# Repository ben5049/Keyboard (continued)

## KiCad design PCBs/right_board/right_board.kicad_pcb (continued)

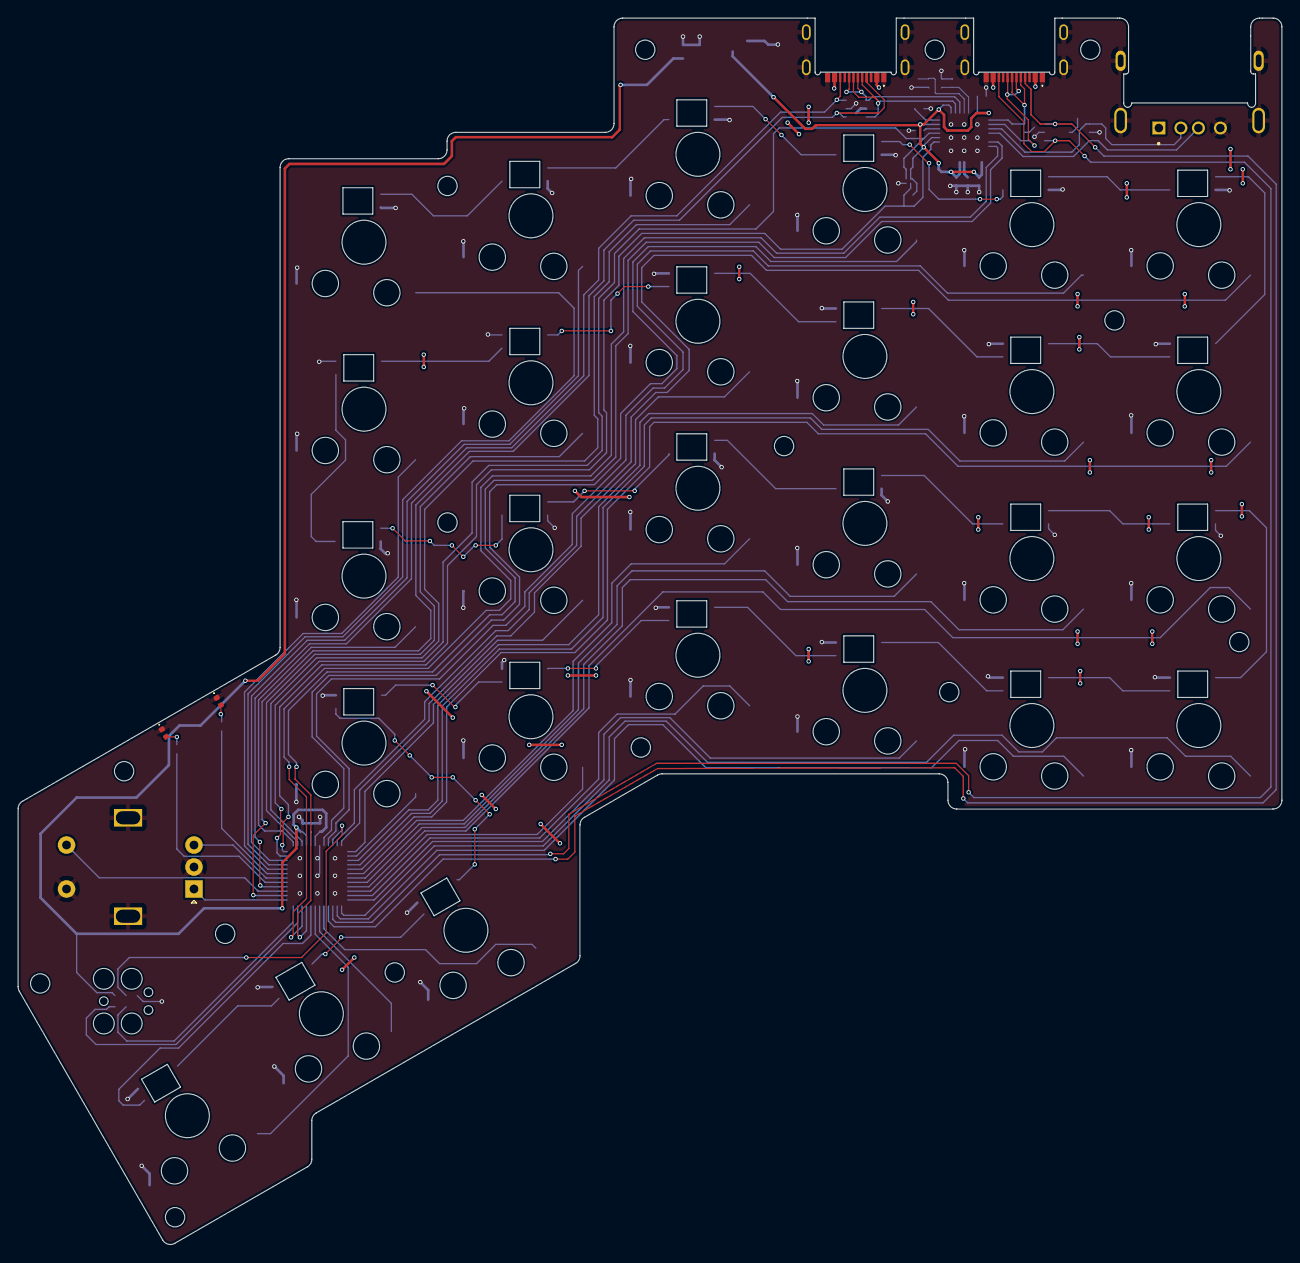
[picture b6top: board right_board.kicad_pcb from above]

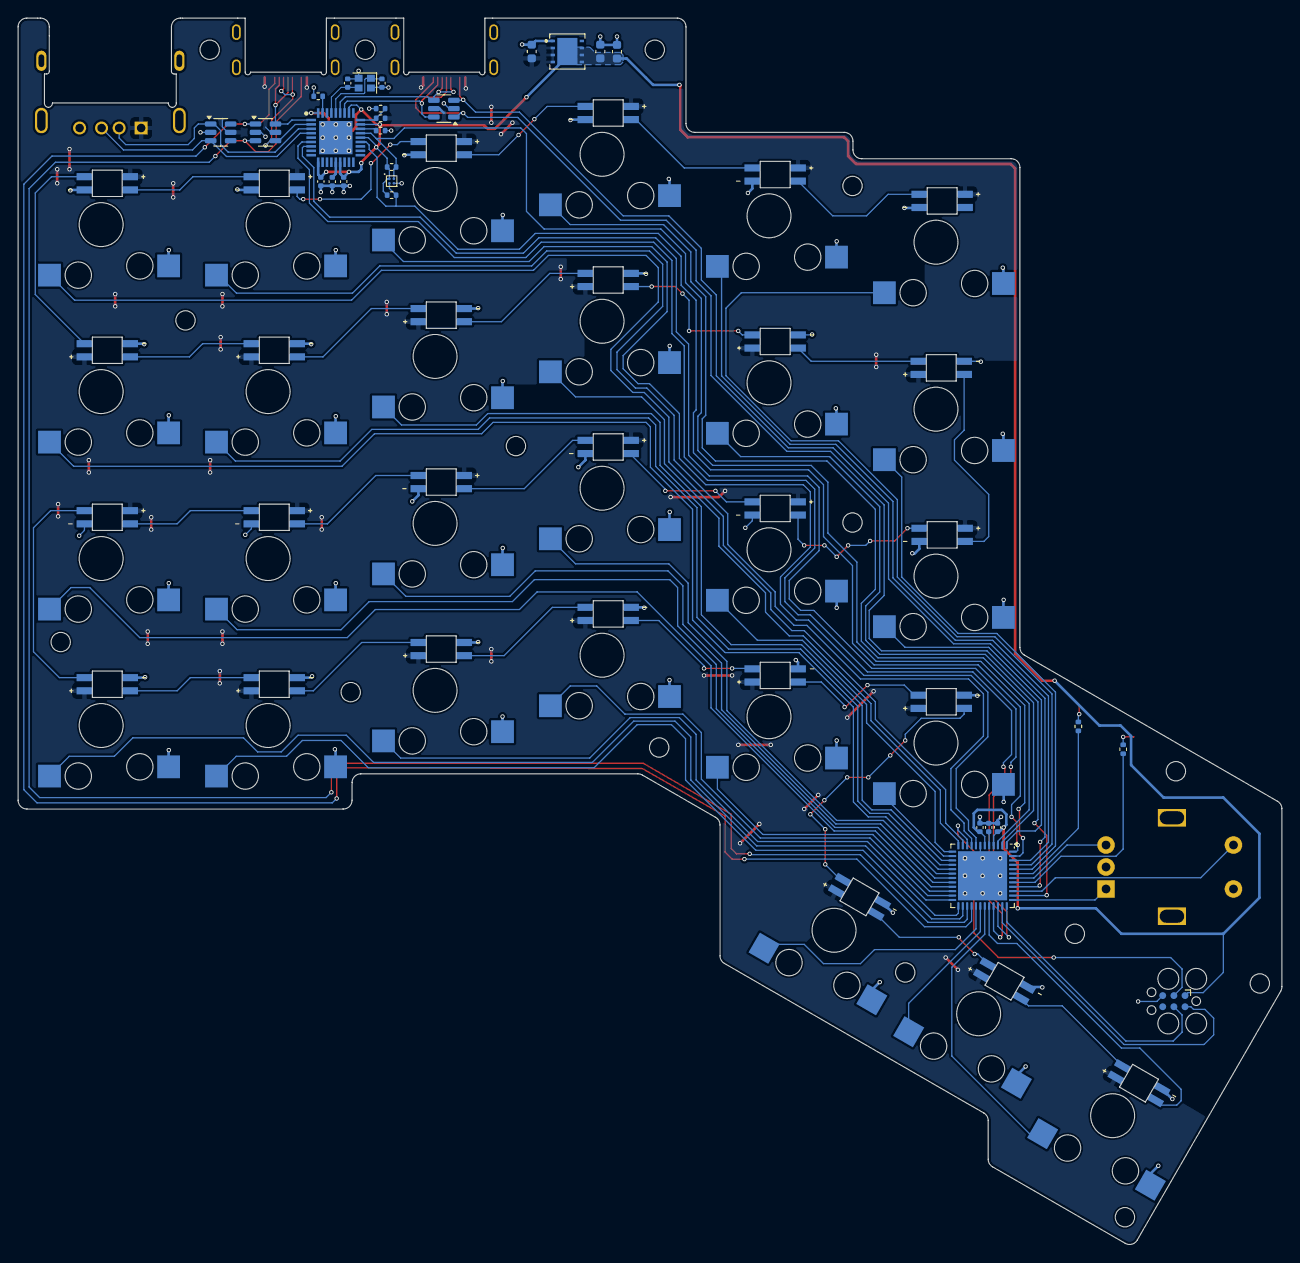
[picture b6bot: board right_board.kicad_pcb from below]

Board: 2 copper layers, 143.8 x 139.6 mm, 88 parts (55 on the bottom side), 88 nets.

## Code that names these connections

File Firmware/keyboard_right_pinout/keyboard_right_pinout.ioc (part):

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Mcu.Name=STM32G0C1C(C-E)Ux
Mcu.Package=UFQFPN48
Mcu.UserName=STM32G0C1CEUx
PA0.GPIOParameters=GPIO_PuPd,GPIO_Label
PA0.GPIO_Label=KEY_A12
PA0.GPIO_PuPd=GPIO_PULLUP
PA0.Signal=GPIO_Input
PA1.GPIOParameters=GPIO_PuPd,GPIO_Label
PA1.GPIO_Label=KEY_B9
PA1.GPIO_PuPd=GPIO_PULLUP
PA1.Signal=GPIO_Input
PA10.GPIOParameters=GPIO_Label
PA10.GPIO_Label=NEOPIXEL
PA10.Signal=S_TIM1_CH3
PA11\ [PA9].Mode=Device
PA11\ [PA9].Signal=USB_DM
PA12\ [PA10].Mode=Device
PA12\ [PA10].Signal=USB_DP
PA13.Mode=Serial_Wire
PA13.Signal=SYS_SWDIO
PA14-BOOT0.Mode=Serial_Wire
PA14-BOOT0.Signal=SYS_SWCLK
PA15.Signal=S_TIM2_CH1_ETR
PA2.GPIOParameters=GPIO_PuPd,GPIO_Label
PA2.GPIO_Label=KEY_C8
PA2.GPIO_PuPd=GPIO_PULLUP
PA2.Signal=GPIO_Input
PA3.GPIOParameters=GPIO_PuPd,GPIO_Label
PA3.GPIO_Label=KEY_D7
PA3.GPIO_PuPd=GPIO_PULLUP
PA3.Signal=GPIO_Input
PA4.GPIOParameters=GPIO_PuPd,GPIO_Label
PA4.GPIO_Label=KEY_B10
PA4.GPIO_PuPd=GPIO_PULLUP
PA4.Signal=GPIO_Input
PA5.GPIOParameters=GPIO_PuPd,GPIO_Label
PA5.GPIO_Label=KEY_B11
PA5.GPIO_PuPd=GPIO_PULLUP
PA5.Signal=GPIO_Input
PA6.GPIOParameters=GPIO_PuPd,GPIO_Label
PA6.GPIO_Label=KEY_B12
PA6.GPIO_PuPd=GPIO_PULLUP
PA6.Signal=GPIO_Input
PA7.GPIOParameters=GPIO_PuPd,GPIO_Label
PA7.GPIO_Label=KEY_C9
PA7.GPIO_PuPd=GPIO_PULLUP
PA7.Signal=GPIO_Input
PA8.Mode=Dual_Role_AllSignals
PA8.Signal=UCPD1_CC1
PA9.GPIOParameters=GPIO_PuPd,GPIO_Label
PA9.GPIO_Label=KEY_E6
PA9.GPIO_PuPd=GPIO_PULLUP
PA9.Signal=GPIO_Input
PB0.GPIOParameters=GPIO_PuPd,GPIO_Label
PB0.GPIO_Label=KEY_C10
PB0.GPIO_PuPd=GPIO_PULLUP
PB0.Signal=GPIO_Input
PB1.GPIOParameters=GPIO_PuPd,GPIO_Label
PB1.GPIO_Label=KEY_C11
PB1.GPIO_PuPd=GPIO_PULLUP
PB1.Signal=GPIO_Input
PB10.GPIOParameters=GPIO_PuPd,GPIO_Label
PB10.GPIO_Label=KEY_D8
PB10.GPIO_PuPd=GPIO_PULLUP
PB10.Signal=GPIO_Input
PB11.GPIOParameters=GPIO_PuPd,GPIO_Label
PB11.GPIO_Label=KEY_D9
PB11.GPIO_PuPd=GPIO_PULLUP
PB11.Signal=GPIO_Input
PB12.GPIOParameters=GPIO_PuPd,GPIO_Label
PB12.GPIO_Label=KEY_D10
PB12.GPIO_PuPd=GPIO_PULLUP
PB12.Signal=GPIO_Input
PB13.GPIOParameters=GPIO_PuPd,GPIO_Label
PB13.GPIO_Label=KEY_D12
PB13.GPIO_PuPd=GPIO_PULLUP
PB13.Signal=GPIO_Input
PB14.GPIOParameters=GPIO_PuPd,GPIO_Label
PB14.GPIO_Label=KEY_D11
PB14.GPIO_PuPd=GPIO_PULLUP
PB14.Signal=GPIO_Input
PB15.Mode=Dual_Role_AllSignals
PB15.Signal=UCPD1_CC2
PB2.GPIOParameters=GPIO_PuPd,GPIO_Label
PB2.GPIO_Label=KEY_C12
PB2.GPIO_PuPd=GPIO_PULLUP
PB2.Signal=GPIO_Input
PB3.Signal=S_TIM2_CH2
PB4.GPIOParameters=GPIO_Label
PB4.GPIO_Label=STAT1_LED
PB4.Signal=GPIO_Output
PB5.GPIOParameters=GPIO_PuPd,GPIO_Label
PB5.GPIO_Label=KEY_B7
PB5.GPIO_PuPd=GPIO_PULLUP
PB5.Signal=GPIO_Input
PB6.GPIOParameters=GPIO_PuPd,GPIO_Label
PB6.GPIO_Label=KEY_A7
PB6.GPIO_PuPd=GPIO_PULLUP
PB6.Signal=GPIO_Input
PB7.GPIOParameters=GPIO_PuPd,GPIO_Label
PB7.GPIO_Label=KEY_A8
PB7.GPIO_PuPd=GPIO_PULLUP
PB7.Signal=GPIO_Input
PB8.Mode=I2C
PB8.Signal=I2C1_SCL
PB9.Mode=I2C
PB9.Signal=I2C1_SDA
PC13.GPIOParameters=GPIO_PuPd,GPIO_Label
PC13.GPIO_Label=KEY_C7
PC13.GPIO_PuPd=GPIO_PULLUP
PC13.Signal=GPIO_Input
PC14-OSC32_IN\ (PC14).GPIOParameters=GPIO_PuPd,GPIO_Label
PC14-OSC32_IN\ (PC14).GPIO_Label=KEY_B8
PC14-OSC32_IN\ (PC14).GPIO_PuPd=GPIO_PULLUP
PC14-OSC32_IN\ (PC14).Signal=GPIO_Input
PC15-OSC32_OUT\ (PC15).GPIOParameters=GPIO_PuPd,GPIO_Label
PC15-OSC32_OUT\ (PC15).GPIO_Label=KEY_A9
PC15-OSC32_OUT\ (PC15).GPIO_PuPd=GPIO_PULLUP
PC15-OSC32_OUT\ (PC15).Signal=GPIO_Input
PC6.GPIOParameters=GPIO_PuPd,GPIO_Label
PC6.GPIO_Label=KEY_E5
PC6.GPIO_PuPd=GPIO_PULLUP
PC6.Signal=GPIO_Input
PC7.GPIOParameters=GPIO_PuPd,GPIO_Label
PC7.GPIO_Label=KEY_E4
PC7.GPIO_PuPd=GPIO_PULLUP
PC7.Signal=GPIO_Input
PD0.Mode=Dual_Role_AllSignals
PD0.Signal=UCPD2_CC1
PD1.GPIOParameters=GPIO_PuPd,GPIO_Label
PD1.GPIO_Label=ENC_SW
PD1.GPIO_PuPd=GPIO_PULLUP
PD1.Signal=GPIO_Input
PD2.Mode=Dual_Role_AllSignals
PD2.Signal=UCPD2_CC2
PD3.GPIOParameters=GPIO_Label
PD3.GPIO_Label=STAT2_LED
PD3.Signal=GPIO_Output
PF0-OSC_IN\ (PF0).GPIOParameters=GPIO_PuPd,GPIO_Label
PF0-OSC_IN\ (PF0).GPIO_Label=KEY_A10
PF0-OSC_IN\ (PF0).GPIO_PuPd=GPIO_PULLUP
PF0-OSC_IN\ (PF0).Signal=GPIO_Input
PF1-OSC_OUT\ (PF1).GPIOParameters=GPIO_PuPd,GPIO_Label
PF1-OSC_OUT\ (PF1).GPIO_Label=KEY_A11
PF1-OSC_OUT\ (PF1).GPIO_PuPd=GPIO_PULLUP
PF1-OSC_OUT\ (PF1).Signal=GPIO_Input
RCC.HSE_VALUE=8000000
RCC.SYSCLKFreq_VALUE=64000000
RCC.SYSCLKSource=RCC_SYSCLKSOURCE_PLLCLK
board=custom

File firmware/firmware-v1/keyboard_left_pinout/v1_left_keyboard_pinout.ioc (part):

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Mcu.Name=STM32G0C1C(C-E)Ux
Mcu.Package=UFQFPN48
Mcu.UserName=STM32G0C1CEUx
PA0.GPIOParameters=GPIO_PuPd,GPIO_Label
PA0.GPIO_Label=KEY_C1
PA0.GPIO_PuPd=GPIO_PULLUP
PA0.Signal=GPIO_Input
PA1.GPIOParameters=GPIO_PuPd,GPIO_Label
PA1.GPIO_Label=KEY_C2
PA1.GPIO_PuPd=GPIO_PULLUP
PA1.Signal=GPIO_Input
PA10.GPIOParameters=GPIO_PuPd,GPIO_Label
PA10.GPIO_Label=KEY_A6
PA10.GPIO_PuPd=GPIO_PULLUP
PA10.Signal=GPIO_Input
PA11\ [PA9].Mode=Device
PA11\ [PA9].Signal=USB_DM
PA12\ [PA10].Mode=Device
PA12\ [PA10].Signal=USB_DP
PA13.Mode=Serial_Wire
PA13.Signal=SYS_SWDIO
PA14-BOOT0.Mode=Serial_Wire
PA14-BOOT0.Signal=SYS_SWCLK
PA15.GPIOParameters=GPIO_PuPd,GPIO_Label
PA15.GPIO_Label=KEY_B6
PA15.GPIO_PuPd=GPIO_PULLUP
PA15.Signal=GPIO_Input
PA2.GPIOParameters=GPIO_PuPd,GPIO_Label
PA2.GPIO_Label=KEY_C3
PA2.GPIO_PuPd=GPIO_PULLUP
PA2.Signal=GPIO_Input
PA3.GPIOParameters=GPIO_PuPd,GPIO_Label
PA3.GPIO_Label=KEY_C4
PA3.GPIO_PuPd=GPIO_PULLUP
PA3.Signal=GPIO_Input
PA4.GPIOParameters=GPIO_PuPd,GPIO_Label
PA4.GPIO_Label=KEY_D5
PA4.GPIO_PuPd=GPIO_PULLUP
PA4.Signal=GPIO_Input
PA5.GPIOParameters=GPIO_PuPd,GPIO_Label
PA5.GPIO_Label=KEY_B1
PA5.GPIO_PuPd=GPIO_PULLUP
PA5.Signal=GPIO_Input
PA6.GPIOParameters=GPIO_PuPd,GPIO_Label
PA6.GPIO_Label=KEY_B2
PA6.GPIO_PuPd=GPIO_PULLUP
PA6.Signal=GPIO_Input
PA7.GPIOParameters=GPIO_PuPd,GPIO_Label
PA7.GPIO_Label=KEY_B3
PA7.GPIO_PuPd=GPIO_PULLUP
PA7.Signal=GPIO_Input
PA8.Mode=Dual_Role_AllSignals
PA8.Signal=UCPD1_CC1
PA9.GPIOParameters=GPIO_PuPd,GPIO_Label
PA9.GPIO_Label=KEY_D6
PA9.GPIO_PuPd=GPIO_PULLUP
PA9.Signal=GPIO_Input
PB0.GPIOParameters=GPIO_PuPd,GPIO_Label
PB0.GPIO_Label=KEY_B4
PB0.GPIO_PuPd=GPIO_PULLUP
PB0.Signal=GPIO_Input
PB1.GPIOParameters=GPIO_PuPd,GPIO_Label
PB1.GPIO_Label=KEY_A1
PB1.GPIO_PuPd=GPIO_PULLUP
PB1.Signal=GPIO_Input
PB10.GPIOParameters=GPIO_PuPd,GPIO_Label
PB10.GPIO_Label=KEY_A2
PB10.GPIO_PuPd=GPIO_PULLUP
PB10.Signal=GPIO_Input
PB11.GPIOParameters=GPIO_PuPd,GPIO_Label
PB11.GPIO_Label=KEY_B5
PB11.GPIO_PuPd=GPIO_PULLUP
PB11.Signal=GPIO_Input
PB12.GPIOParameters=GPIO_PuPd,GPIO_Label
PB12.GPIO_Label=KEY_A3
PB12.GPIO_PuPd=GPIO_PULLUP
PB12.Signal=GPIO_Input
PB13.Mode=I2C
PB13.Signal=I2C2_SCL
PB14.Mode=I2C
PB14.Signal=I2C2_SDA
PB15.Mode=Dual_Role_AllSignals
PB15.Signal=UCPD1_CC2
PB2.GPIOParameters=GPIO_PuPd,GPIO_Label
PB2.GPIO_Label=KEY_C5
PB2.GPIO_PuPd=GPIO_PULLUP
PB2.Signal=GPIO_Input
PB3.GPIOParameters=GPIO_Label
PB3.GPIO_Label=STAT2_LED
PB3.Signal=GPIO_Output
PB4.GPIOParameters=GPIO_Label
PB4.GPIO_Label=ENC_A
PB4.Signal=S_TIM3_CH1
PB5.GPIOParameters=GPIO_Label
PB5.GPIO_Label=ENC_B
PB5.Signal=S_TIM3_CH2
PB6.GPIOParameters=GPIO_PuPd,GPIO_Label
PB6.GPIO_Label=ENC_SW
PB6.GPIO_PuPd=GPIO_PULLUP
PB6.Signal=GPIO_Input
PB7.GPIOParameters=GPIO_Label
PB7.GPIO_Label=NEOPIXEL
PB7.Signal=S_TIM4_CH2
PB8.GPIOParameters=GPIO_PuPd,GPIO_Label
PB8.GPIO_Label=KEY_E3
PB8.GPIO_PuPd=GPIO_PULLUP
PB8.Signal=GPIO_Input
PB9.GPIOParameters=GPIO_PuPd,GPIO_Label
PB9.GPIO_Label=KEY_E2
PB9.GPIO_PuPd=GPIO_PULLUP
PB9.Signal=GPIO_Input
PC13.GPIOParameters=GPIO_PuPd,GPIO_Label
PC13.GPIO_Label=KEY_E1
PC13.GPIO_PuPd=GPIO_PULLUP
PC13.Signal=GPIO_Input
PC14-OSC32_IN\ (PC14).GPIOParameters=GPIO_PuPd,GPIO_Label
PC14-OSC32_IN\ (PC14).GPIO_Label=KEY_D1
PC14-OSC32_IN\ (PC14).GPIO_PuPd=GPIO_PULLUP
PC14-OSC32_IN\ (PC14).Signal=GPIO_Input
PC15-OSC32_OUT\ (PC15).GPIOParameters=GPIO_PuPd,GPIO_Label
PC15-OSC32_OUT\ (PC15).GPIO_Label=KEY_D2
PC15-OSC32_OUT\ (PC15).GPIO_PuPd=GPIO_PULLUP
PC15-OSC32_OUT\ (PC15).Signal=GPIO_Input
PC6.GPIOParameters=GPIO_PuPd,GPIO_Label
PC6.GPIO_Label=KRY_A4
PC6.GPIO_PuPd=GPIO_PULLUP
PC6.Signal=GPIO_Input
PC7.GPIOParameters=GPIO_PuPd,GPIO_Label
PC7.GPIO_Label=KEY_A5
PC7.GPIO_PuPd=GPIO_PULLUP
PC7.Signal=GPIO_Input
PD0.Mode=Dual_Role_AllSignals
PD0.Signal=UCPD2_CC1
PD1.GPIOParameters=GPIO_PuPd,GPIO_Label
PD1.GPIO_Label=KEY_C6
PD1.GPIO_PuPd=GPIO_PULLUP
PD1.Signal=GPIO_Input
PD2.Mode=Dual_Role_AllSignals
PD2.Signal=UCPD2_CC2
PD3.GPIOParameters=GPIO_Label
PD3.GPIO_Label=STAT1_LED
PD3.Signal=GPIO_Output
PF0-OSC_IN\ (PF0).GPIOParameters=GPIO_PuPd,GPIO_Label
PF0-OSC_IN\ (PF0).GPIO_Label=KEY_D3
PF0-OSC_IN\ (PF0).GPIO_PuPd=GPIO_PULLUP
PF0-OSC_IN\ (PF0).Signal=GPIO_Input
PF1-OSC_OUT\ (PF1).GPIOParameters=GPIO_PuPd,GPIO_Label
PF1-OSC_OUT\ (PF1).GPIO_Label=KEY_D4
PF1-OSC_OUT\ (PF1).GPIO_PuPd=GPIO_PULLUP
PF1-OSC_OUT\ (PF1).Signal=GPIO_Input
RCC.HSE_VALUE=8000000
RCC.SYSCLKFreq_VALUE=64000000
RCC.SYSCLKSource=RCC_SYSCLKSOURCE_PLLCLK
board=custom

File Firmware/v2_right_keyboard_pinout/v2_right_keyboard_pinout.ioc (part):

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Mcu.Name=STM32U5G9ZJJxQ
Mcu.Package=UFBGA144
Mcu.UserName=STM32U5G9ZJJxQ
PA11.Mode=Internal_Phy_Device
PA11.Signal=USB_OTG_HS_DM
PA12.Mode=Internal_Phy_Device
PA12.Signal=USB_OTG_HS_DP
PA13\ (JTMS/SWDIO).Mode=Serial_Wire
PA13\ (JTMS/SWDIO).Signal=DEBUG_JTMS-SWDIO
PA14\ (JTCK/SWCLK).Mode=Serial_Wire
PA14\ (JTCK/SWCLK).Signal=DEBUG_JTCK-SWCLK
PB15.Signal=S_TIM15_CH2
PB7.Mode=DSIHost_Adapted_TE
PB7.Signal=DSIHOST_TE
PC12.Signal=UART5_TX
PD8.Mode=Asynchronous
PD8.Signal=USART3_TX
PD9.Mode=Asynchronous
PD9.Signal=USART3_RX
PG10.Mode=Asynchronous
PG10.Signal=USART1_RX
PG13.Mode=I2C
PG13.Signal=I2C1_SDA
PG14.Mode=I2C
PG14.Signal=I2C1_SCL
PG9.Mode=Asynchronous
PG9.Signal=USART1_TX
PH0-OSC_IN\ (PH0).Mode=HSE-External-Oscillator
PH0-OSC_IN\ (PH0).Signal=RCC_OSC_IN
PH1-OSC_OUT\ (PH1).Mode=HSE-External-Oscillator
PH1-OSC_OUT\ (PH1).Signal=RCC_OSC_OUT
RCC.HSE_VALUE=16000000
board=custom

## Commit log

2024-05-12 Layout done, need to route.
2024-05-12 Updated gitignore
2024-05-13 Left board routing half done
2024-05-13 Removed broken library
2024-05-13 Redoing libraries
2024-05-13 Libraries redo done
2024-05-13 Libraries redo actually done
2024-05-13 Left board done
2024-05-14 Right board done, all components ordered
2024-05-16 BOM and README updates
2024-05-17 Pinout updates
2024-05-17 Pinouts finished
2024-05-18 Enclosure v1 finished
2024-05-18 Created PCB BOMs & LED covers
2024-05-19 Added USBX examples to Examples/
2024-05-19 Added USBX examples to /Examples
2024-05-20 USB Progress, need to rewrite device descriptors.
2024-05-20 USB Device descriptor wrangling done
2024-05-21 USBPD API is a mess
2024-05-25 Blink and neopixels work (mostly). Added Future changes document.
2024-05-27 USB Hub working and keyboard device class working
2024-05-27 Alpha-numeric keys work, need to sync modifier keys.
2024-05-28 Key struct updated to include modifier keys and layer switching.
2024-05-28 Modifiers work properly for left half.
2024-05-30 Both halves work. Next is adding layers.
2024-05-31 Knobs work
2024-06-10 Knobs work properly
2024-06-24 Layers working
2024-07-08 V2 Started
2024-07-08 V2 progress
2024-07-10 Display schematic done
2024-07-11 V2 Schematic mostly done
2024-07-11 Added debug header footprint
2024-07-13 Schematic mostly done, moving onto PCB
2024-07-13 Started routing
2024-07-14 Layout in progress
2024-07-15 Layout progress
2024-07-15 Placement done
2024-07-18 395 Unrouted
2024-07-19 339 Unrouted
2024-07-20 279 Unrouted
2024-07-21 249 Unrouted
2024-09-27 Backing up changes
2026-02-08 Added component library to v3
2026-02-08 Moved v1 & v2 and started v3
2026-02-09 Deleted delmes
2026-02-09 Moved v1 left firmware
2026-02-10 Updated right-control-board layout
2026-02-10 Added allowed component area to right-key-board
2026-02-11 Right control board schematic almost done
2026-02-12 Key board schematic done and layout half done
2026-02-13 Added FPC panel
2026-02-14 Right daughter boards finished
2026-02-14 Removed old example code
2026-02-14 Move old firmware to new folders
2026-02-15 Added unfinished ZMK firmware
2026-02-15 Updated control-board firmware repo
2026-02-16 Added debug-breakout board, progress on right side schematics & layout
2026-02-16 Added power gate to AS5600 to reduce its sleep current
2026-02-17 Right control board placement and schematic done
2026-02-18 Right control board ~50 unrouted
2026-02-19 Right control board routing finished
2026-02-21 Added mounting holes
2026-02-22 Moved charging LED
2026-02-23 Finished debug breakout board and added 5V voltage sensing to key board
2026-02-28 Left key board done
2026-03-01 Left knob board done
2026-03-01 Left control board done
2026-03-02 Keyboard v3 hardware done
2026-03-15 Added v3 left BOMs and updated buck inductor
